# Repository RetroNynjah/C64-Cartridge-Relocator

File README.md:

# Retroninja C64 Cartridge Relocator
90 degree adapter for mounting a C64 cartridge vertically

The top/front side of the cartridge should be facing the computer.

Edge connector that should fit: ‎395-044-520-201‎	https://www.digikey.se/product-detail/sv/395-044-520-201/151-1428-ND/559822?itemSeq=381630769

Capactitor is a 100nF ceramic cap with 5mm pitch. For good measure. Other values could work or even no capacitor at all.

Reset button is optional but a 6x6mm tactile switch is suitable and always nice to have.

fierodoug has designed a 3d-printable enclosure for this board. The design can be found on Thingiverse at https://www.thingiverse.com/thing:5159147

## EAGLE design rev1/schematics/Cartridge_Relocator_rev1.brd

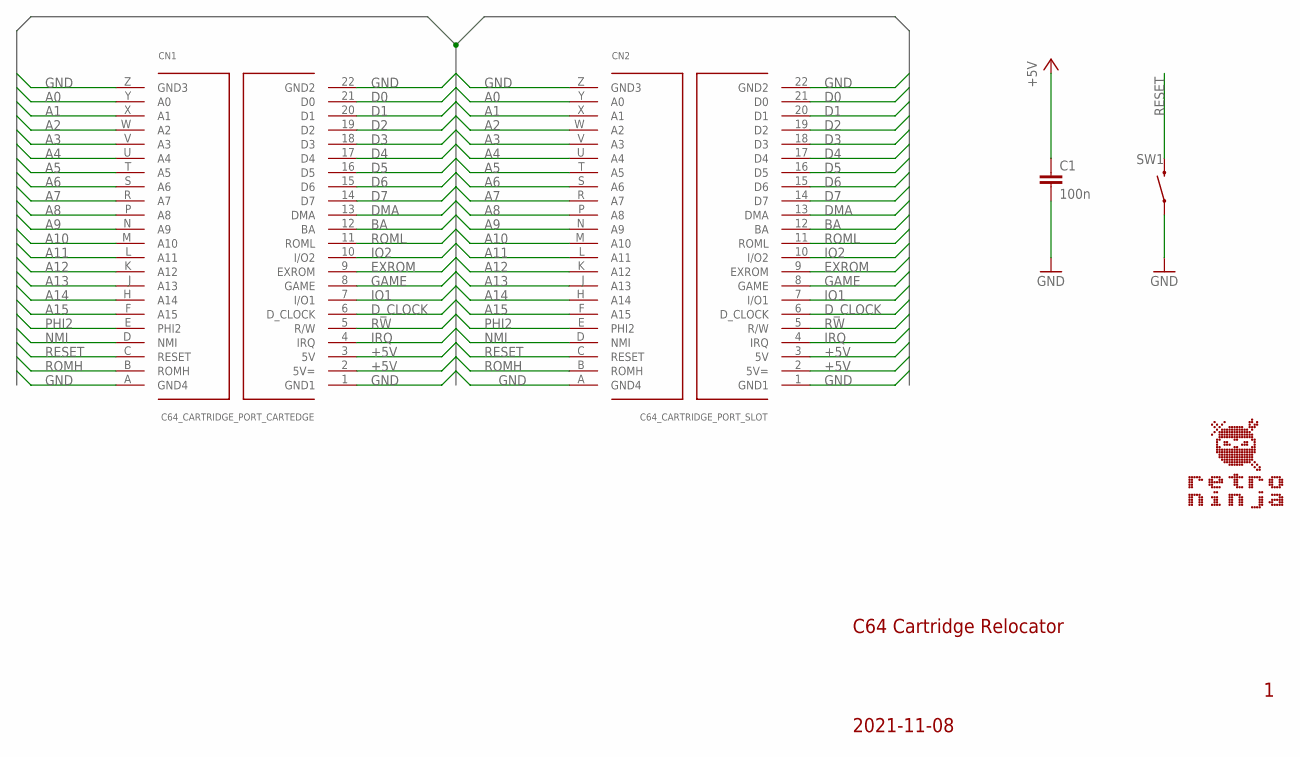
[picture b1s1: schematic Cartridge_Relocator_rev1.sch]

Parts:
C1: 100n; CAP_5MM_2.5X5.0_ROUND
CN1: C64_CARTRIDGE_PORT_CARTEDGE; C64_CARTRIDGE_BOARDEDGE
CN2: C64_CARTRIDGE_PORT_SLOT; C64_CARTRIDGE_SLOT
SW1: SWITCH_MOMENTARY; SWITCH_MOM_6.0MMX5.0MM

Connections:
+5V: C1.1, CN1.2 (5V=), CN1.3 (5V), CN2.2 (5V=), CN2.3 (5V)
A0: CN1.Y (A0), CN2.Y (A0)
A1: CN1.X (A1), CN2.X (A1)
A2: CN1.W (A2), CN2.W (A2)
A3: CN1.V (A3), CN2.V (A3)
A4: CN1.U (A4), CN2.U (A4)
A5: CN1.T (A5), CN2.T (A5)
A6: CN1.S (A6), CN2.S (A6)
A7: CN1.R (A7), CN2.R (A7)
A8: CN1.P (A8), CN2.P (A8)
A9: CN1.N (A9), CN2.N (A9)
A10: CN1.M (A10), CN2.M (A10)
A11: CN1.L (A11), CN2.L (A11)
A12: CN1.K (A12), CN2.K (A12)
A13: CN1.J (A13), CN2.J (A13)
A14: CN1.H (A14), CN2.H (A14)
A15: CN1.F (A15), CN2.F (A15)
BA: CN1.12 (BA), CN2.12 (BA)
D0: CN1.21 (D0), CN2.21 (D0)
D1: CN1.20 (D1), CN2.20 (D1)
D2: CN1.19 (D2), CN2.19 (D2)
D3: CN1.18 (D3), CN2.18 (D3)
D4: CN1.17 (D4), CN2.17 (D4)
D5: CN1.16 (D5), CN2.16 (D5)
D6: CN1.15 (D6), CN2.15 (D6)
D7: CN1.14 (D7), CN2.14 (D7)
DMA: CN1.13 (DMA), CN2.13 (DMA)
D_CLOCK: CN1.6 (D_CLOCK), CN2.6 (D_CLOCK)
EXROM: CN1.9 (EXROM), CN2.9 (EXROM)
GAME: CN1.8 (GAME), CN2.8 (GAME)
GND: C1.2, CN1.1 (GND1), CN1.22 (GND2), CN1.A (GND4), CN1.Z (GND3), CN2.1 (GND1), CN2.22 (GND2), CN2.A (GND4), CN2.Z (GND3), SW1.1, SW1.2 (1)
IO1: CN1.7 (I/O1), CN2.7 (I/O1)
IO2: CN1.10 (I/O2), CN2.10 (I/O2)
IRQ: CN1.4 (IRQ), CN2.4 (IRQ)
NMI: CN1.D (NMI), CN2.D (NMI)
PHI2: CN1.E (PHI2), CN2.E (PHI2)
RESET: CN1.C (RESET), CN2.C (RESET), SW1.3 (2), SW1.4 (2)
ROMH: CN1.B (ROMH), CN2.B (ROMH)
ROML: CN1.11 (ROML), CN2.11 (ROML)
RW: CN1.5 (R/W), CN2.5 (R/W)

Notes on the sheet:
2021-11-08
C64 Cartridge Relocator

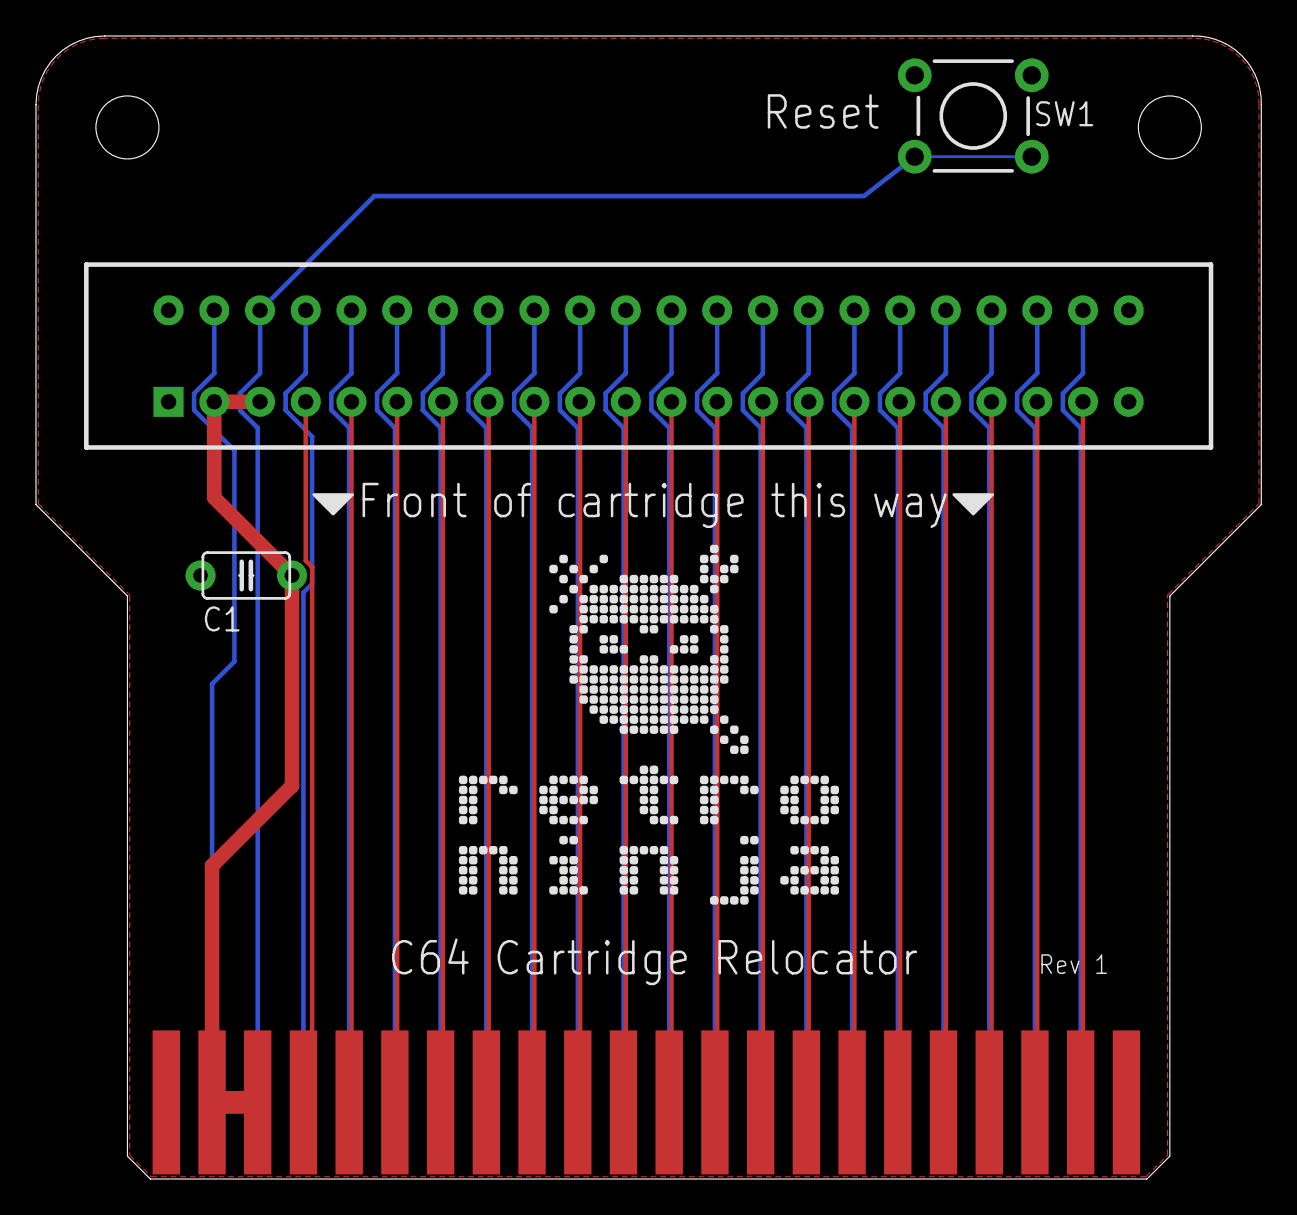
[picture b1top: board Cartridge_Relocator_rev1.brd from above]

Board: 2 copper layers, 68.1 x 63.5 mm, 6 parts (1 on the bottom side), 40 nets.

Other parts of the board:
U$1: RETRONINJA_20MM
U$2: OSHW_16MM

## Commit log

2021-11-08 Minor update to board, images and gerbers
2021-11-08 Added rendered image
2021-11-08 Updated image
2022-05-02 Link to enclosure
2025-02-16 Rev 2 PCB
    New revision of PCB without ground planes
